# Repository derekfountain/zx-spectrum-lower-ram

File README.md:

# zx-spectrum-lower-ram

## A lower RAM module for the ZX Spectrum

This is a hardware module which implements the lower 16K RAM bank for a
16K or 48K ZX Spectrum microcomputer.

The memory bank is normally implemented with 8 4116 DRAM ICs. These
ICs are no longer in production, and although not yet hard to get hold
of, the ones which are available are 50 years old and have inevitable
frailties. This project implements the required 16K of memory using a
modern SRAM IC.

The project is a plug in replacement, replacing this:

with this:

(And yes, that's a different Spectrum in those 2 photos. :))

At the time of implemention, there was no open source design for this type
of memory board. Hence I created one.

## Design

The Spectrum uses a multiplexed address system common of low cost micros of
the 70s and 80s. It addresses the memory ICs twice, first with a 7-bit row
address ("RAS") value, then about 50ns later with a 7-bit column address
("CAS") value. That's how the 4116 ICs work. The advange to those ICs is
that it only requires 7 address lines, rather than the 14 which would
otherwise be required to address 16K.

None of that is required any more and modern RAM ICs have all the address
lines they require. The modern design is therefore to use a latch triggered on the row
address strobe (RAS) to store the first 7 bits of the address, then pass those and
the other 7 bits of the address into the address lines of a modern
SRAM IC when the CAS signal arrives. It turns out that the SRAM will remove
its data from its output bus slightly too soon for the Spectrum's ULA, so
a small timer circuit is needed to slow the CAS signal down a few nanoseconds.

16K SRAMs are difficult to get hold of these days, and tend to be rather
expensive. This project uses a 32K SRAM and ignores the top 16K of it.

I've only tested the design with the Ferranti 6C001E-6 and Ferranti 6C001E-7
ULAs. It's possible some timing tweaks might be required for other ULAs.

## KiCAD Project

The project is implemented in KiCAD v6. It's in the slrm/ directory. ((S)pectrum
(L)ower ( R)AM (M)odule.)

There are a couple of snapshots of early implementations of the project. One of
these is a "breakout" version of the board which might be useful to
investigate signals using a 'scope.

## Fabrication

The Gerber files which can be sent directly for fabrication are to be found
in slrm/fab1.2/fab1.2.zip. You can just upload that ZIP to JLCPCB (which is
what I did). Default values for JLCPCB's fabrication process
will do fine except for the board thickness. Set that to 1.00mm. It's very
tight under the Spectrum's keyboard.

## Bill of Materials

1x [IS62C256AL-25ULI-TR 32K SRAM](https://www.mouser.co.uk/ProductDetail/870-62C256AL-25ULIT)
32K SRAM IC
<br>
1x [74HCT574](https://www.mouser.co.uk/ProductDetail/595-SN74HCT574NSR)
8 bit flip flop latch
<br>
1x [74HCT04](https://www.mouser.co.uk/ProductDetail/863-MC74HCT04ADG)
6 circuit inverter
<br>
3x [3216 SMD 0.1uF capacitor](https://www.mouser.co.uk/ProductDetail/581-12065C104KAT4A)
Capacitor
<br>
1x [3216 68R SMD resistor](https://www.mouser.co.uk/ProductDetail/603-RT1206FRE0768RL)
Resistor
<br>
1x [3216 SMD 100pF capacitor](https://www.mouser.co.uk/ProductDetail/581-12065A101J)
Capacitor
<br>
22x Arduino type 2.54mm Pin header connectors

## Assembly

Any 62256-standard SRAM IC should work. The ISSI one I chose was the cheapest
at Mouser. The [Alliance Memory](https://www.mouser.co.uk/ProductDetail/913-CY62256NLL55SNXI)
one should be fine as well. Solder the SRAM first, then do the latch and the inverter, then
their decoupling capacitors. Then do the resistor and capacitor for the timer circuit.
Through the hole footprints are also available for these last two components, but they make
the keyboard refit extremely tight. They work, but use SMD if you can.

## Pin Length

The pins need to protrude below the board and fit into the sockets (or PCB if you're
soldering directly), but they mustn't be any longer than absolutely necessary
otherwise the board will stand too proud on the Spectrum PCB and the keyboard won't
fit back on.

The correct length for all the boards I've made up is 4.2mm protruding. This is very
difficult to get accurate and consistent with cutters, so I made a 3D printed jig.
That's in the slrm/3D directory, both as an SCAD source file and a STL file. If you
take this route, place the jig over the pins:

then use a rotary tool or similar to grind the pins to the correct length:

## Fitting

Once assembled, and with the pins the right length, the board then just presses into
the sockets on the Spectrum PCB:

Note the fitting: the board doesn't span the entire width of the 8 4116 ICs. The outer
most sides of the two end sockets aren't used.

## More Information

There's a bit more information on how it works on [my website](https://www.derekfountain.org/my_zx_lower_ram.php),
and a few more photos and discussion on it over at
[Spectrum Computing](https://spectrumcomputing.co.uk/forums/viewtopic.php?t=8782).

[Derek Fountain](https://www.derekfountain.org/), January 2023

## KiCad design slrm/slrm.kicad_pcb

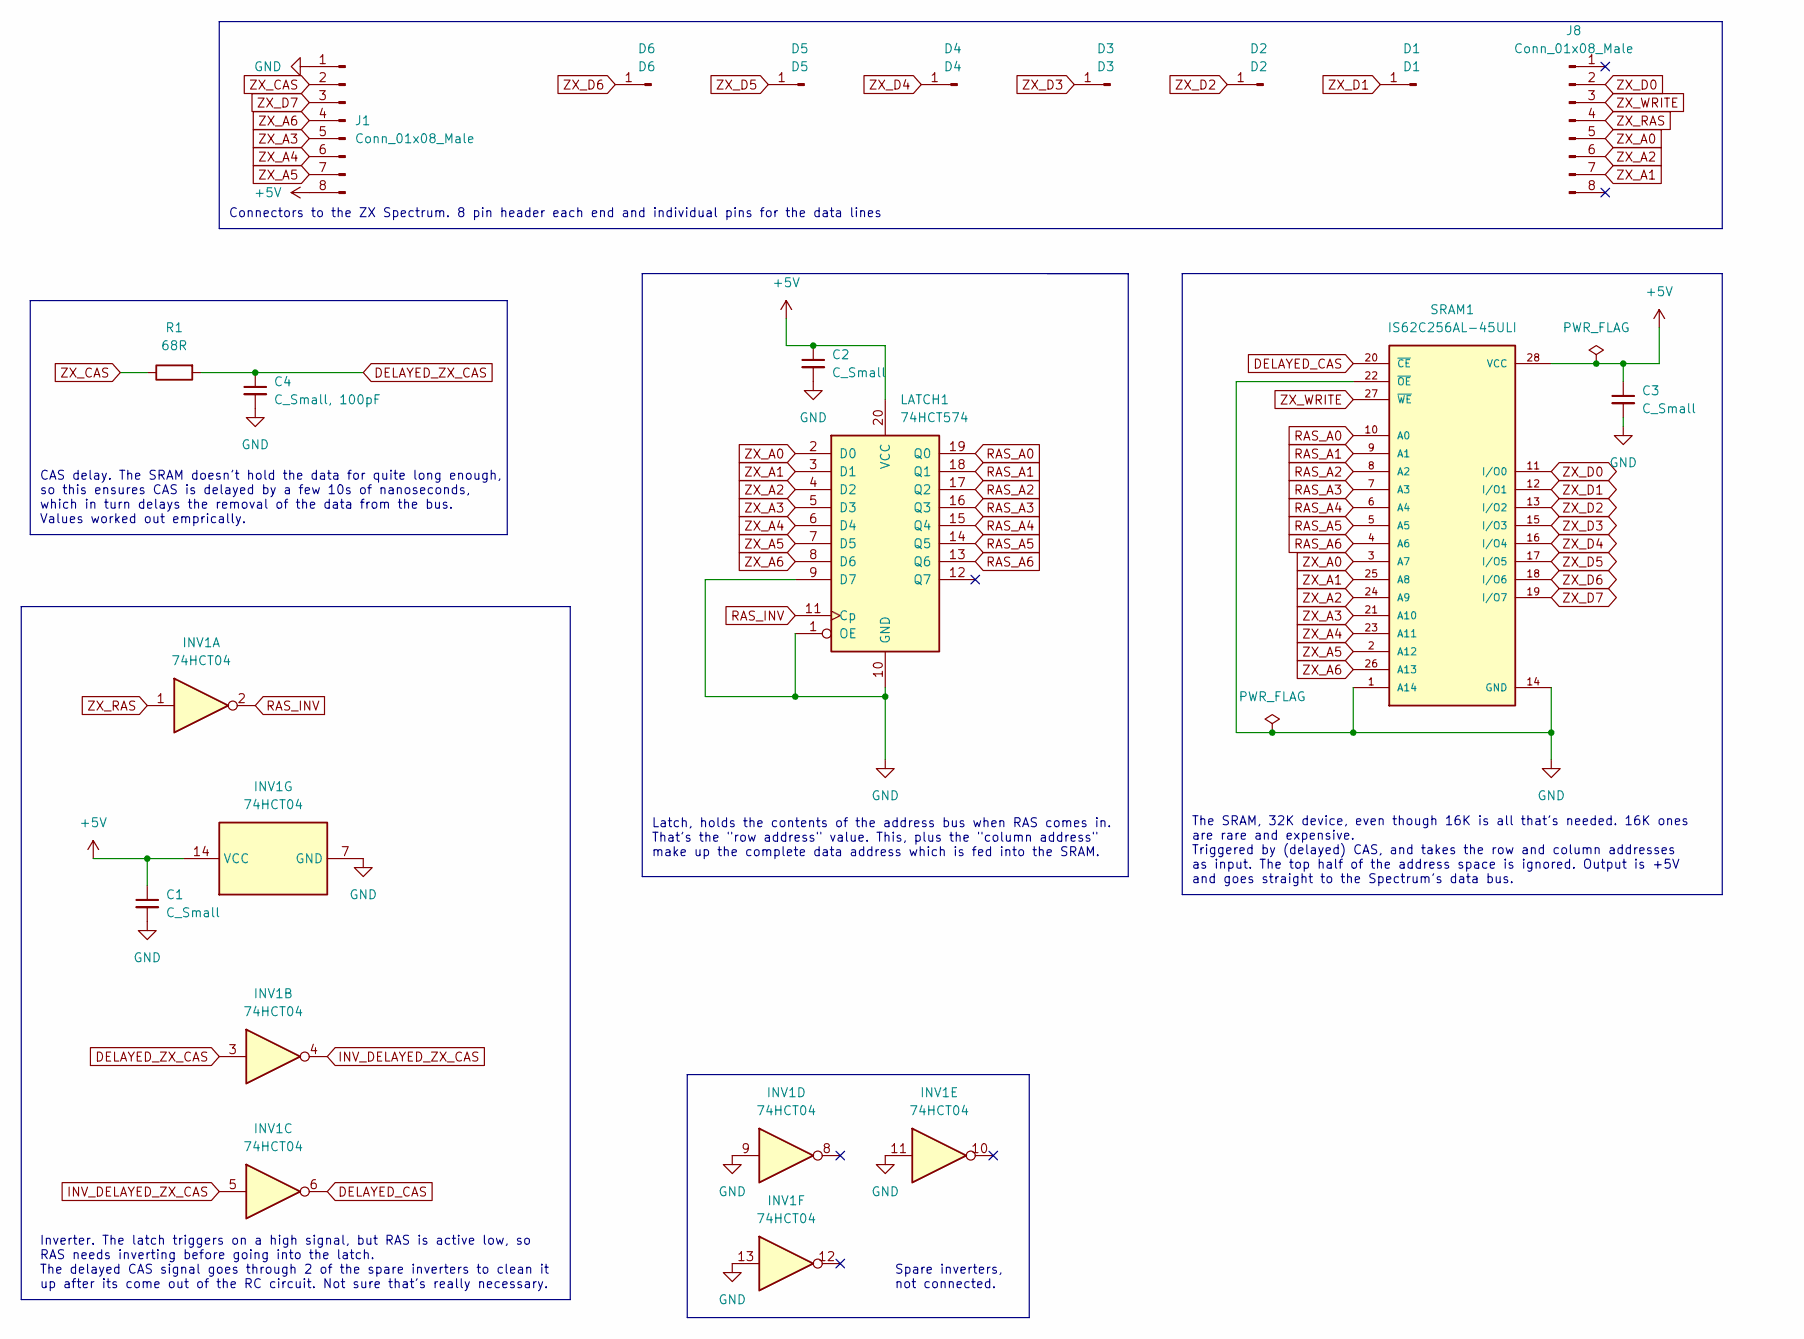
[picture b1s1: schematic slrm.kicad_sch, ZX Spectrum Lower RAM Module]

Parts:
C1, C2, C3: C_Small; C_1206_3216Metric
C4: C_Small, 100pF; C_Disc_D4.3mm_W1.9mm_P5.00mm
D1: D1; PinHeader_1x01_P2.00mm_Vertical
D2: D2; PinHeader_1x01_P2.00mm_Vertical
D3: D3; PinHeader_1x01_P2.00mm_Vertical
D4: D4; PinHeader_1x01_P2.00mm_Vertical
D5: D5; PinHeader_1x01_P2.00mm_Vertical
D6: D6; PinHeader_1x01_P2.00mm_Vertical
INV1: 74HCT04; SOIC-14_3.9x8.7mm_P1.27mm
J1, J8: Conn_01x08_Male; PinHeader_1x08_P2.54mm_Vertical
LATCH1: 74HCT574; SO-20_5.3x12.6mm_P1.27mm
R1: 68R; R_Axial_DIN0207_L6.3mm_D2.5mm_P10.16mm_Horizontal
SRAM1: IS62C256AL-45ULI; SOIC127P1210X305-28N

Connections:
+5V: C1.1, C2.1, C3.1, INV1.14 (VCC), J1.8, LATCH1.20 (VCC), SRAM1.28 (VCC)
DELAYED_CAS: INV1.6, SRAM1.20 (~CE)
DELAYED_ZX_CAS: C4.1, INV1.3, R1.2; also elsewhere on the board
GND: C1.2, C2.2, C3.2, C4.2, INV1.7 (GND), INV1.9, INV1.11, INV1.13, J1.1, LATCH1.1 (OE), LATCH1.9 (D7), LATCH1.10 (GND), SRAM1.1 (A14), SRAM1.14 (GND), SRAM1.22 (~OE); also elsewhere on the board
INV_DELAYED_ZX_CAS: INV1.4, INV1.5
RAS_A0: LATCH1.19 (Q0), SRAM1.10 (A0)
RAS_A1: LATCH1.18 (Q1), SRAM1.9 (A1)
RAS_A2: LATCH1.17 (Q2), SRAM1.8 (A2)
RAS_A3: LATCH1.16 (Q3), SRAM1.7 (A3)
RAS_A4: LATCH1.15 (Q4), SRAM1.6 (A4)
RAS_A5: LATCH1.14 (Q5), SRAM1.5 (A5)
RAS_A6: LATCH1.13 (Q6), SRAM1.4 (A6)
RAS_INV: INV1.2, LATCH1.11 (Cp)
ZX_A0: J8.5, LATCH1.2 (D0), SRAM1.3 (A7)
ZX_A1: J8.7, LATCH1.3 (D1), SRAM1.25 (A8)
ZX_A2: J8.6, LATCH1.4 (D2), SRAM1.24 (A9)
ZX_A3: J1.5, LATCH1.5 (D3), SRAM1.21 (A10)
ZX_A4: J1.6, LATCH1.6 (D4), SRAM1.23 (A11)
ZX_A5: J1.7, LATCH1.7 (D5), SRAM1.2 (A12)
ZX_A6: J1.4, LATCH1.8 (D6), SRAM1.26 (A13)
ZX_CAS: J1.2, R1.1
ZX_D0: J8.2, SRAM1.11 (I/O0)
ZX_D1: D1.1, SRAM1.12 (I/O1)
ZX_D2: D2.1, SRAM1.13 (I/O2)
ZX_D3: D3.1, SRAM1.15 (I/O3)
ZX_D4: D4.1, SRAM1.16 (I/O4)
ZX_D5: D5.1, SRAM1.17 (I/O5)
ZX_D6: D6.1, SRAM1.18 (I/O6)
ZX_D7: J1.3, SRAM1.19 (I/O7)
ZX_RAS: INV1.1, J8.4
ZX_WRITE: J8.3, SRAM1.27 (~WE)

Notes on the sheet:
Inverter. The latch triggers on a high signal, but RAS is active low, so RAS needs inverting before going into the latch. The delayed CAS signal goes through 2 of the spare inverters to clean it up after its come out of the RC circuit. Not sure that's really necessary.
Connectors to the ZX Spectrum. 8 pin header each end and individual pins for the data lines
Latch, holds the contents of the address bus when RAS comes in. That's the "row address" value. This, plus the "column address" make up the complete data address which is fed into the SRAM.
CAS delay. The SRAM doesn't hold the data for quite long enough, so this ensures CAS is delayed by a few 10s of nanoseconds, which in turn delays the removal of the data from the bus. Values worked out emprically.
Spare inverters, not connected.
The SRAM, 32K device, even though 16K is all that's needed. 16K ones are rare and expensive. Triggered by (delayed) CAS, and takes the row and column addresses as input. The top half of the address space is ignored. Output is +5V and goes straight to the Spectrum's data bus.

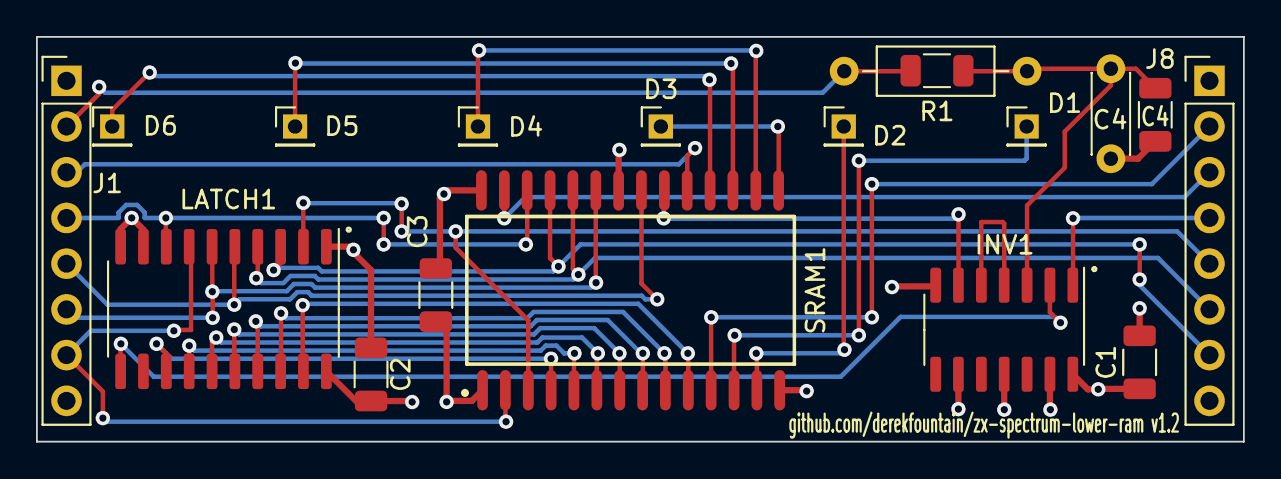
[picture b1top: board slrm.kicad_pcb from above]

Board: 4 copper layers, 67.1 x 22.5 mm, 17 parts (0 on the bottom side), 31 nets.

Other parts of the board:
C4#2: C_Small; C_1206_3216Metric

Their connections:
DELAYED_ZX_CAS: C4#2.2; also elsewhere on the board
GND: C4#2.1; also elsewhere on the board

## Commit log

2022-10-04 schematic worth keeping
2022-10-04 more schematic work, ground inputs, find the footprint for the sram
2022-10-05 split out zx connections into individual connectors, power to the inverter
2022-10-05 use the right connectors
2022-10-06 layout complete
2022-10-06 final tweaks
2022-10-06 v1.0, fab files sent off
2022-10-29 work towards fab2
2022-11-07 v1.1, added RC circuit to main design, added a breakout version (debug) and a duplication of a working circuit
2022-12-28 remove some backups
2022-12-28 version 1.2 gerbers created
2023-01-04 bit of a tidy up
2023-01-15 v1.2 photos and 3d print of jig
2023-01-15 README for v1.2
2023-01-15 final updates
2023-01-16 images and readme updates
